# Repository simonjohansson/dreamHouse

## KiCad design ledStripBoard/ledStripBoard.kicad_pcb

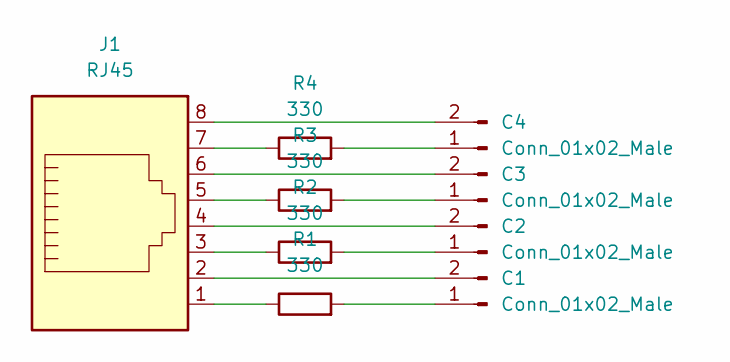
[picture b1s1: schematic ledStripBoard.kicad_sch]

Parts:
C1, C2, C3, C4: Conn_01x02_Male; PinSocket_1x02_P2.54mm_Vertical
J1: RJ45; RJ45_Amphenol_54602-x08_Horizontal
R1, R2, R3, R4: 330; R_Axial_DIN0414_L11.9mm_D4.5mm_P20.32mm_Horizontal

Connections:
unnamed: C1.1, R1.2
unnamed: C2.1, R2.2
unnamed: C3.1, R3.2
unnamed: C4.1, R4.2
unnamed: J1.1, R1.1
unnamed: C1.2, J1.2
unnamed: J1.3, R2.1
unnamed: C2.2, J1.4
unnamed: J1.5, R3.1
unnamed: C3.2, J1.6
unnamed: J1.7, R4.1
unnamed: C4.2, J1.8

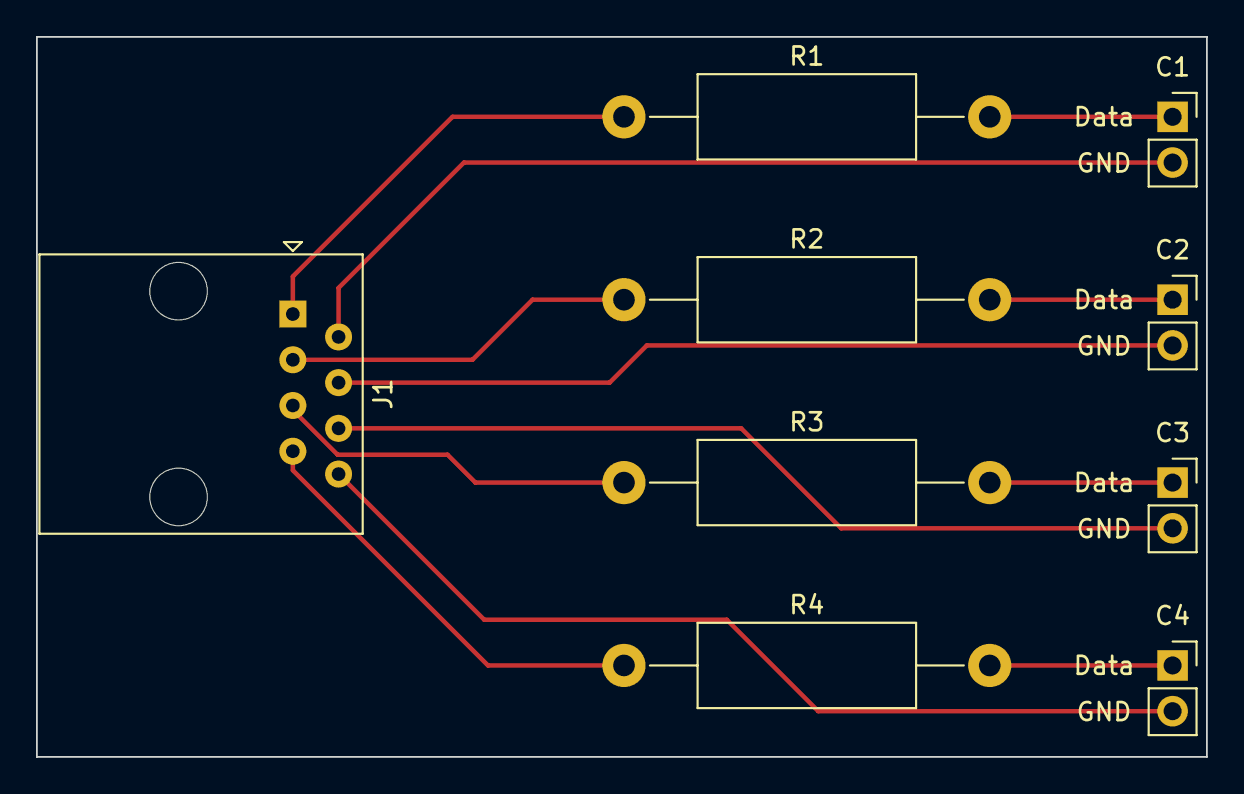
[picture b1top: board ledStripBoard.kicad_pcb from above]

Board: 2 copper layers, 65.0 x 40.0 mm, 9 parts (0 on the bottom side), 12 nets.

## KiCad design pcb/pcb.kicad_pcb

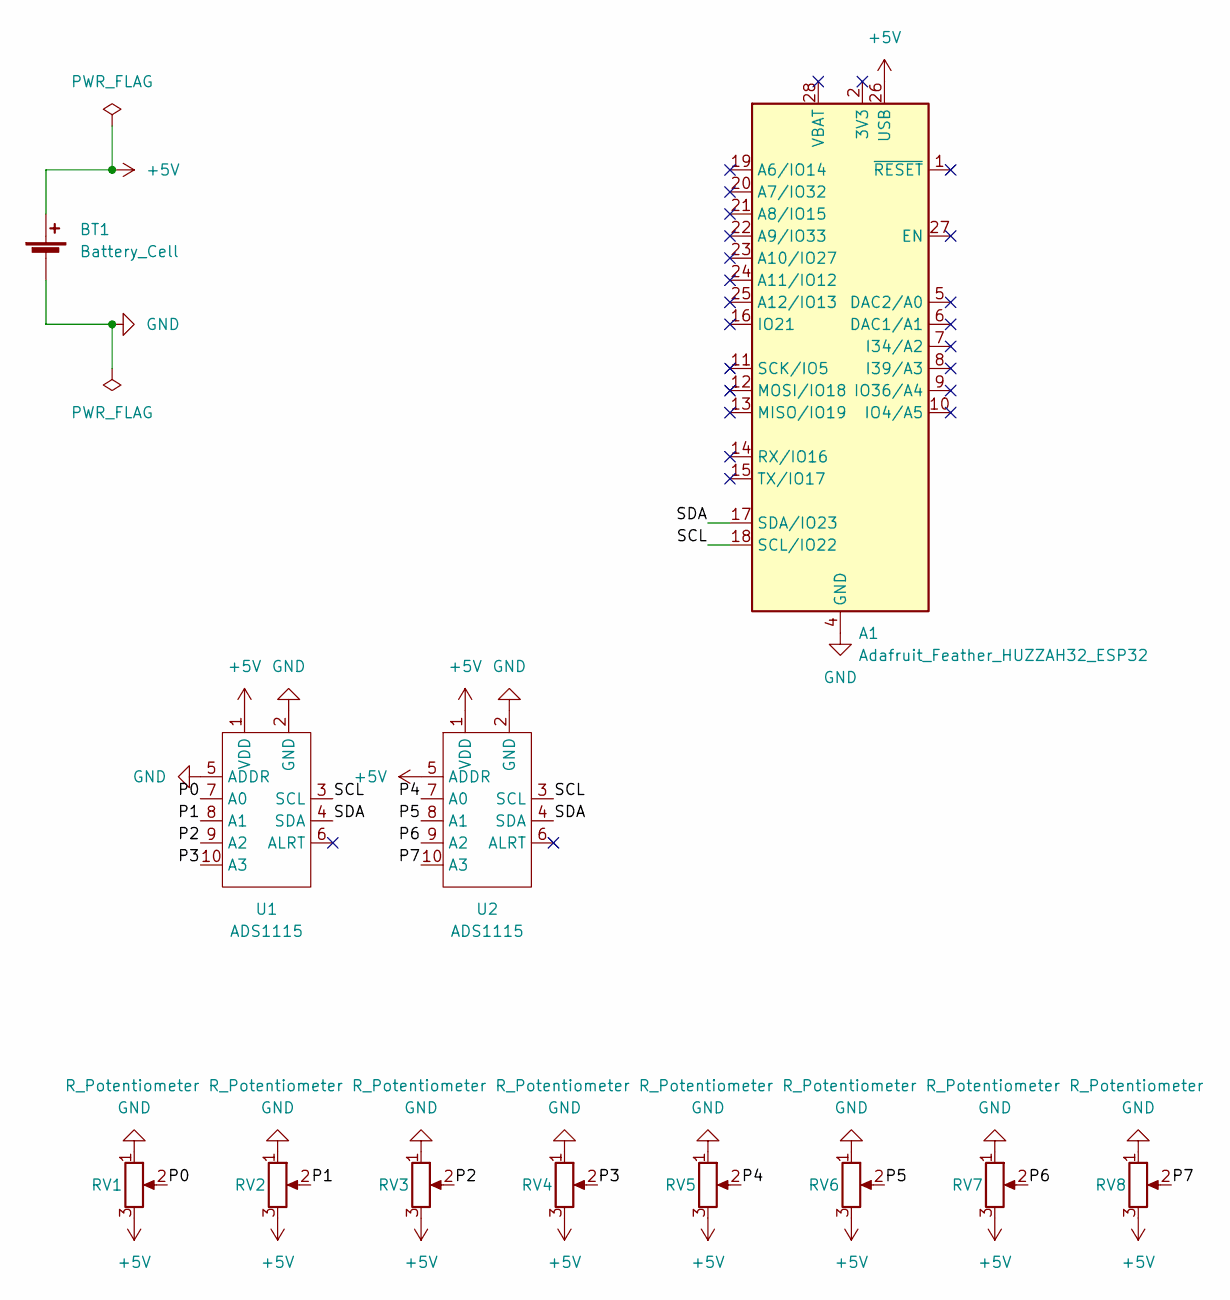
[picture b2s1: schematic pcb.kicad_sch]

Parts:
A1: Adafruit_Feather_HUZZAH32_ESP32; Adafruit_Feather
BT1: Battery_Cell; SolderWire-0.25sqmm_1x02_P4.2mm_D0.65mm_OD1.7mm
RV1, RV2, RV3, RV4, RV5, RV6, RV7, RV8: R_Potentiometer; PinHeader_1x03_P2.54mm_Vertical
U1, U2: ADS1115; PinSocket_1x10_P2.54mm_Vertical

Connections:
+5V: A1.26 (USB), BT1.1 (+), RV1.3, RV2.3, RV3.3, RV4.3, RV5.3, RV6.3, RV7.3, RV8.3, U1.1 (VDD), U2.1 (VDD), U2.5 (ADDR)
/P0: RV1.2, U1.7 (A0)
/P1: RV2.2, U1.8 (A1)
/P2: RV3.2, U1.9 (A2)
/P3: RV4.2, U1.10 (A3)
/P4: RV5.2, U2.7 (A0)
/P5: RV6.2, U2.8 (A1)
/P6: RV7.2, U2.9 (A2)
/P7: RV8.2, U2.10 (A3)
/SCL: A1.18 (SCL/IO22), U1.3 (SCL), U2.3 (SCL)
/SDA: A1.17 (SDA/IO23), U1.4 (SDA), U2.4 (SDA)
GND: A1.4 (GND), BT1.2 (-), RV1.1, RV2.1, RV3.1, RV4.1, RV5.1, RV6.1, RV7.1, RV8.1, U1.2 (GND), U1.5 (ADDR), U2.2 (GND)

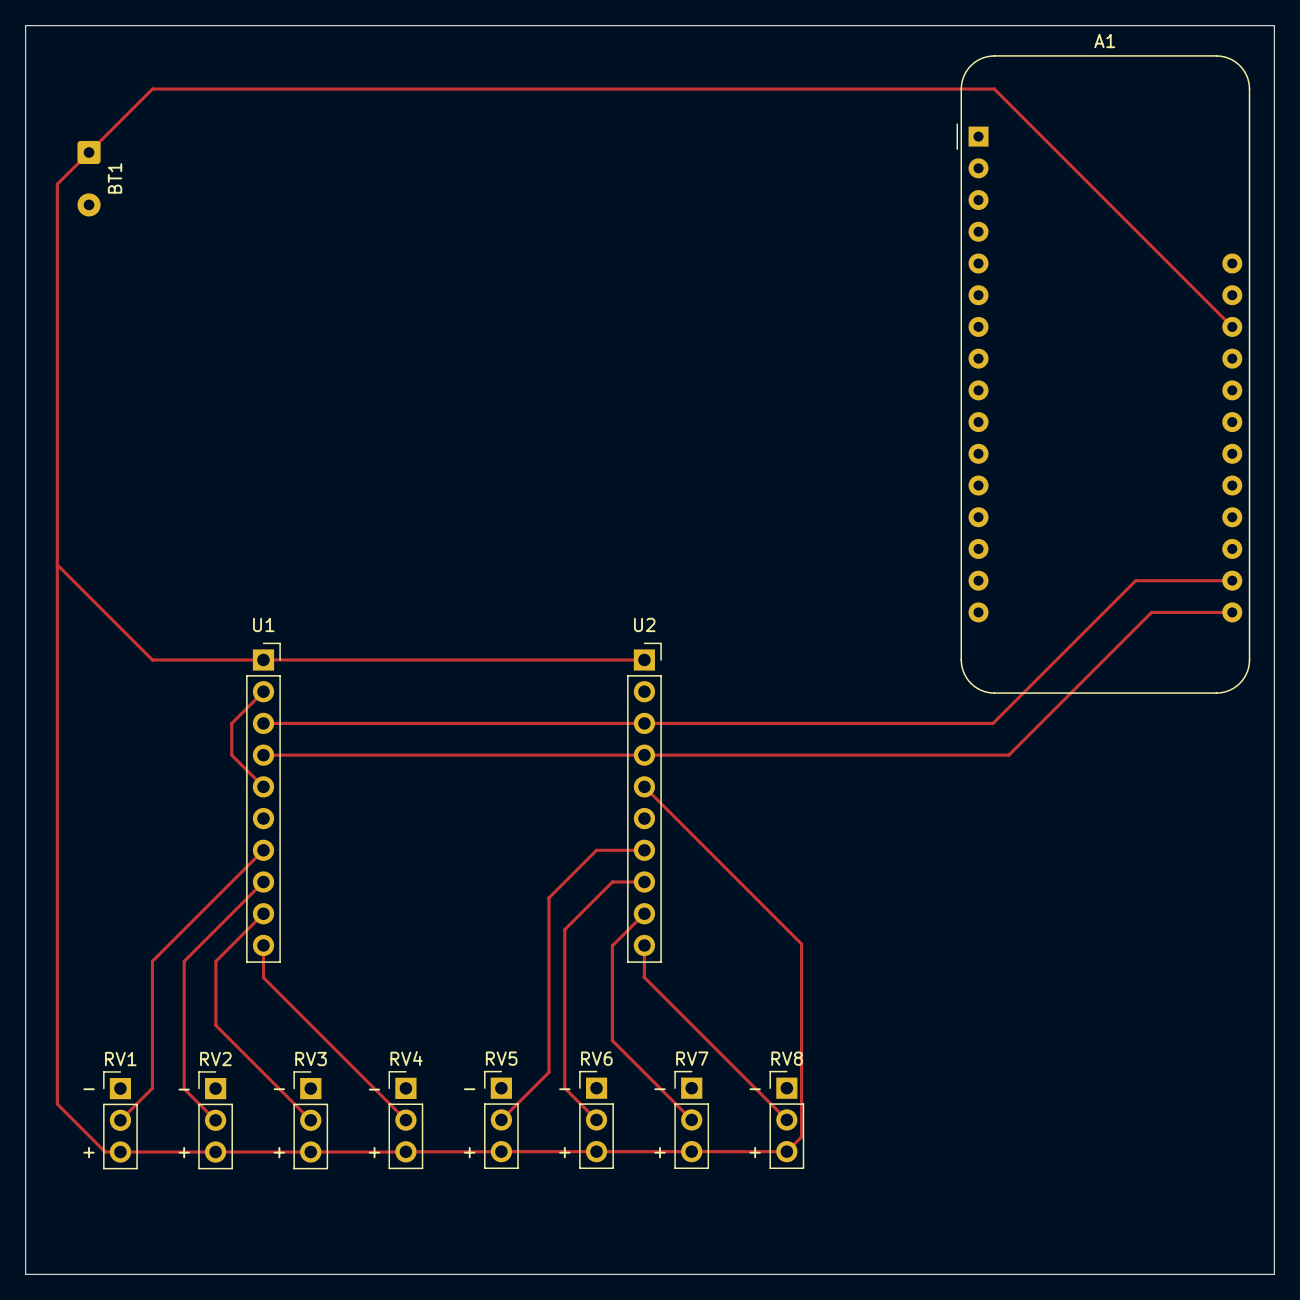
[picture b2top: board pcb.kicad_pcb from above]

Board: 2 copper layers, 100.0 x 100.0 mm, 12 parts (0 on the bottom side), 12 nets.

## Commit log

2022-08-03 Different files for different tasks
2022-08-03 Different colour modes
2022-08-03 Brightness
2022-08-04 Empty kicad project
2022-08-04 Initial PCB
2022-08-04 One handle is enough..
2022-08-05 Add crude potentiometer calibration
2022-08-05 Use a proper logging library instead of Serial.printx... Configure clang-format to allow longer line lenghts.. We're not in the 80's anymore.
2022-08-06 oled display task
2022-08-06 Led task should recieve the leds trough DI
2022-08-07 State not state
2022-08-07 Different loops for different colour modes
2022-08-07 Add a scan mode that scans trough the HSV colours
2022-08-09 Random mode
2022-08-09 Trace mode, and use a mutex so that we dont cancel a task in the middle of a FastLED.show() thus bugging out the led strip
2022-08-09 Call State PotState instead, since Wifi seems to expose State. Also use esp_random since its better
2022-08-15 Fixes weird interrupt issue between WiFi and FastLED causing flickering
2022-08-15 WIP, two strips
2022-08-19 PCB breakout for led strips
2022-08-28 4 strips
